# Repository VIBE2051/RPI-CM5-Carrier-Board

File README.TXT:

# CM5 Module PCB with On-Board Cube Module

## Overview
This project involves the design and implementation of a custom PCB featuring the Raspberry Pi Compute Module 5 (CM5) integrated with an on-board Cube module. The PCB is tailored for embedded applications, offering robust connectivity, GPIO access, and flexibility for a wide range of use cases.

## Features
- **Compute Module 5 (CM5) Integration**:
  - Harnesses the power of the Raspberry Pi CM5 for computational tasks.
  - High-density DF40 connectors provide extensive GPIO and peripheral access.

- **On-Board Cube Module**:
  - Supports CubePilot's Cube Module for advanced flight control and navigation.
  - Provides seamless communication between the CM5 and Cube Module.

- **Key Interfaces**:
  - **GPIO Access**: Full access to CM5 GPIOs for customization and flexibility.
  - **Peripheral Support**: Integrated connections for UART, I2C, SPI, CAN, and PWM.
  - **Power Management**: Dedicated power regulation circuits for stable operation.

- **Compact Design**:
  - Optimized for embedded systems with a small form factor.
  - Designed for ease of integration into various enclosures and setups.

## Applications
- **Autonomous Systems**:
  - Ideal for robotics and UAVs requiring compute-intensive processing.
- **IoT Devices**:
  - Suitable for smart devices leveraging Raspberry Pi's ecosystem.
- **Embedded Prototyping**:
  - Flexible platform for developing custom applications.

## Pinout Information
The PCB exposes the GPIOs and other interfaces from the CM5 and Cube Module through accessible connectors. Key pinout details:

- **DF40 Connectors** for CM5:
  - GPIO, UART, I2C, SPI, PWM, and power signals.
  
- **Cube Module DF17 80-Pin Connector**:
  - Interfaces with peripherals such as sensors, GPS, and external modules.

## Design Highlights
- **High-Density Connector Compatibility**:
  - Provides access to all necessary pins while maintaining a clean layout.
- **Grounding and Power Integrity**:
  - Ensures stable operation even in noisy environments.
- **Robust Mounting Points**:
  - Mechanical design supports secure mounting for reliable deployment.

## Getting Started
1. **Assembly**:
   - Populate the PCB with the required components according to the BOM.
   - Insert the CM5 module into its DF40 connector and secure it.
   - Attach the Cube module to the dedicated 80-pin DF17 connector.

2. **Power Up**:
   - Connect a 5V power supply to the designated power input.
   - Verify power integrity using onboard status LEDs.

3. **Development**:
   - Use Raspberry Pi tools to configure and program the CM5.
   - Interface with the Cube module using compatible software (e.g., ArduPilot, PX4).

## Resources
- **Datasheets**:
  - [CM5 Datasheet](https://datasheets.raspberrypi.com/cm5/cm5-datasheet.pdf)
  - [CubePilot Module Pinout](https://docs.cubepilot.org/)
- **KiCad Files**:
  - Schematic and PCB design files are available in the project repository.
- **Software**:
  - Compatible with Raspberry Pi OS and CubePilot firmware.

## Contributing
Contributions to this project are welcome! Please fork the repository and submit a pull request for any improvements or fixes.

## License
This project is licensed under the MIT License. See the LICENSE file for details.

---

**Contact**: For support or inquiries, please contact [your email/organization].

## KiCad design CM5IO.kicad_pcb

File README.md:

# CM5 Module PCB with On-Board Cube Module

## Overview
This project involves the design and implementation of a custom PCB featuring the Raspberry Pi Compute Module 5 (CM5) integrated with an on-board Cube module. The PCB is tailored for embedded applications, offering robust connectivity, GPIO access, and flexibility for a wide range of use cases.

## Features
- **Compute Module 5 (CM5) Integration**:
  - Harnesses the power of the Raspberry Pi CM5 for computational tasks.
  - High-density DF40 connectors provide extensive GPIO and peripheral access.

- **On-Board Cube Module**:
  - Supports CubePilot's Cube Module for advanced flight control and navigation.
  - Provides seamless communication between the CM5 and Cube Module.

- **Key Interfaces**:
  - **GPIO Access**: Full access to CM5 GPIOs for customization and flexibility.
  - **Peripheral Support**: Integrated connections for UART, I2C, SPI, CAN, and PWM.
  - **Power Management**: Dedicated power regulation circuits for stable operation.

- **Compact Design**:
  - Optimized for embedded systems with a small form factor.
  - Designed for ease of integration into various enclosures and setups.

## Applications
- **Autonomous Systems**:
  - Ideal for robotics and UAVs requiring compute-intensive processing.
- **IoT Devices**:
  - Suitable for smart devices leveraging Raspberry Pi's ecosystem.
- **Embedded Prototyping**:
  - Flexible platform for developing custom applications.

## Pinout Information
The PCB exposes the GPIOs and other interfaces from the CM5 and Cube Module through accessible connectors. Key pinout details:

- **DF40 Connectors** for CM5:
  - GPIO, UART, I2C, SPI, PWM, and power signals.
  
- **Cube Module DF17 80-Pin Connector**:
  - Interfaces with peripherals such as sensors, GPS, and external modules.

## Design Highlights
- **High-Density Connector Compatibility**:
  - Provides access to all necessary pins while maintaining a clean layout.
- **Grounding and Power Integrity**:
  - Ensures stable operation even in noisy environments.
- **Robust Mounting Points**:
  - Mechanical design supports secure mounting for reliable deployment.

## Getting Started
1. **Assembly**:
   - Populate the PCB with the required components according to the BOM.
   - Insert the CM5 module into its DF40 connector and secure it.
   - Attach the Cube module to the dedicated 80-pin DF17 connector.

2. **Power Up**:
   - Connect a 5V power supply to the designated power input.
   - Verify power integrity using onboard status LEDs.

3. **Development**:
   - Use Raspberry Pi tools to configure and program the CM5.
   - Interface with the Cube module using compatible software (e.g., ArduPilot, PX4).

## Resources
- **Datasheets**:
  - [CM5 Datasheet](https://datasheets.raspberrypi.com/cm5/cm5-datasheet.pdf)
  - [CubePilot Module Pinout](https://docs.cubepilot.org/)
- **KiCad Files**:
  - Schematic and PCB design files are available in the project repository.
- **Software**:
  - Compatible with Raspberry Pi OS and CubePilot firmware.

## Contributing
Contributions to this project are welcome! Please fork the repository and submit a pull request for any improvements or fixes.

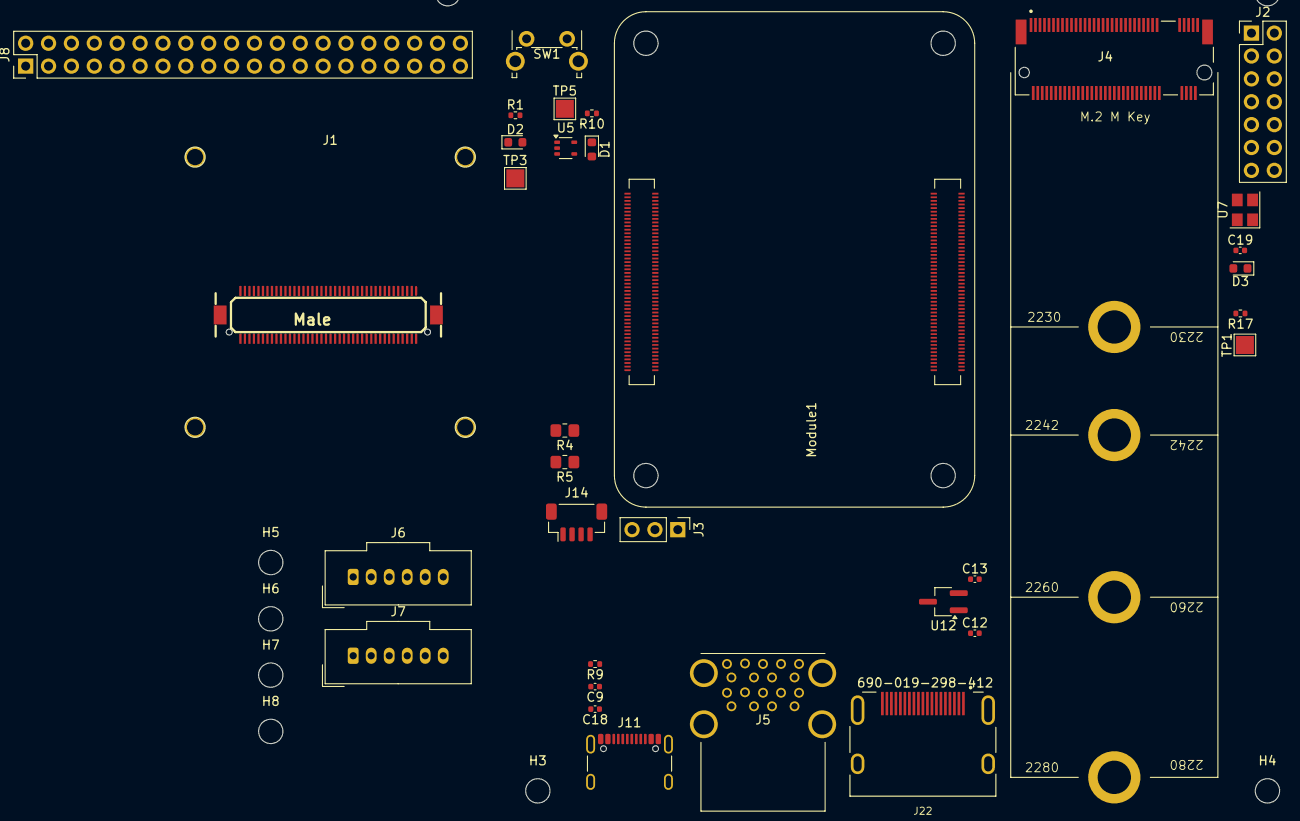
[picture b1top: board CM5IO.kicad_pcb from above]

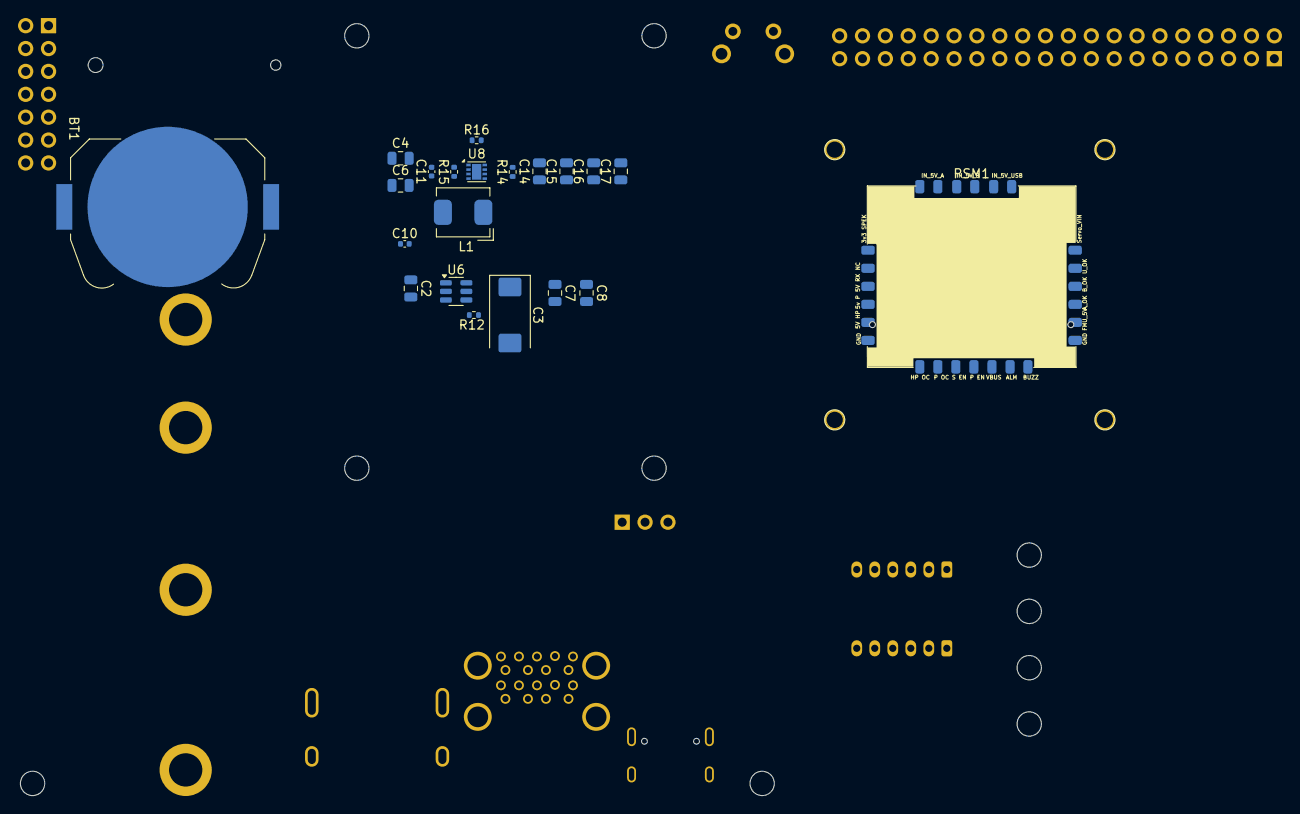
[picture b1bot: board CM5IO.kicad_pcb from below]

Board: 4 copper layers, 62 parts (21 on the bottom side), 105 nets, no tracks yet.

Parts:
BT1: Battery_Cell; BatteryHolder_Keystone_3034_1x20mm
C2, C4, C6, C7, C8, C14, C15, C16, C17: 10u; C_0805_2012Metric
C3: 100uF; CP_EIA-7343-31_Kemet-D
C9, C10, C12, C13, C18, C19: 100n; C_0402_1005Metric
C11: 4.7nF; C_0402_1005Metric
D1: LED Red; LED_0603_1608Metric
D2, D3: LED Green; LED_0603_1608Metric
H1, H2, H3, H4, H5, H6, H7, H8: MountingHole; MountingHole_2.7mm_M2.5_DIN965
J1: DF17_1.0H_-80DP-0.5V_57_; CON-DF17-80M
J2: Conn_02x07_Odd_Even; PinHeader_2x07_P2.54mm_Vertical
J3: Conn_01x03; PinHeader_1x03_P2.54mm_Vertical
J4: Bus_M.2_Socket_M; M.2 M Key socket
J5: USB3_A; MTCONN_UBAF30-D2011
J6, J7: Conn_01x06_Socket; Molex_MicroClasp_55932-0630_1x06_P2.00mm_Vertical
J8: THD-20-R; PinHeader_2x20_P2.54mm_Vertical
J11: USB_C_Receptacle_USB2.0; USB_C_Receptacle_GCT_USB4105-xx-A_16P_TopMnt_Horizontal
J14: JST_SHBM04B-SRSS-TB; JST_SH_BM04B-SRSS-TB_1x04-1MP_P1.00mm_Vertical
J22: 690-019-298-412; EDAC 690-019-298-412
L1: 2.2uH; L_Bourns_SRP5030CC
Module1: ComputeModule5-CM5; Raspberry-Pi-5-Compute-Module
PSM1: Power Selection module; PSM
R1, R10, R17: 1k; R_0402_1005Metric
R4: nf; R_0805_2012Metric_Pad1.20x1.40mm_HandSolder
R5: 0R; R_0805_2012Metric_Pad1.20x1.40mm_HandSolder
R9, R16: 2.2K 1%; R_0402_1005Metric
R12: 15K 1%; R_0402_1005Metric
R14: 100K 1%; R_0402_1005Metric
R15: 10K 1%; R_0402_1005Metric
SW1: Right angle Tact button; SW_Tactile_SPST_Angled_PTS645Vx58-2LFS
TP1, TP3, TP5: TestPoint; TestPoint_Pad_2.0x2.0mm
U5: 74LVC1G07SE-7; SOT-353_SC-70-5
U6: AP22653W6; SOT-23-6
U7: ASEK-32.768KHZ-L-R-T; Crystal_SMD_3225-4Pin_3.2x2.5mm
U8: AP3441SHE-7B; DFN-8-1EP_2x2mm_P0.5mm_EP1.05x1.75mm
U12: RT9742SNGV; TSOT-23_HandSoldering

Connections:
/+3.3v: D1.2 (A), D2.2 (A), J8.1, J8.17, Module1.84 (+3.3v_(Output)), Module1.86 (+3.3v_(Output)), R5.1, U5.5 (VCC)
/+5v: C2.1, C4.1, C6.1, C9.1, C10.1, C12.1, C18.1, J8.2, J8.4, J11.A4 (VBUS), J11.A9 (VBUS), J11.B4 (VBUS), J11.B9 (VBUS), J14.1, Module1.77 (+5v_(Input)), Module1.79 (+5v_(Input)), Module1.81 (+5v_(Input)), Module1.83 (+5v_(Input)), Module1.85 (+5v_(Input)), Module1.87 (+5v_(Input)), R9.1, U6.1 (IN), U8.3 (VIN), U12.1 (IN)
/CC1: J11.A5 (CC1), Module1.94 (CC1)
/CC2: J11.B5 (CC2), Module1.96 (CC2)
/CM5_GPIO ( Ethernet, GPIO, SDCARD)/+1.8v: Module1.88 (+1.8v_(Output)), Module1.90 (+1.8v_(Output)), R4.1
/CM5_GPIO ( Ethernet, GPIO, SDCARD)/BT_nDis: J3.3, Module1.91 (BT_nDisable)
/CM5_GPIO ( Ethernet, GPIO, SDCARD)/Cube_PSM_GPIO/BUZZER_OUT: J7.5, PSM1.BUZZER_OUT (BUZZ_OUT)
/CM5_GPIO ( Ethernet, GPIO, SDCARD)/Cube_PSM_GPIO/VDD_5V_BRICK: J6.1, J6.2, PSM1.VDD_BRICK_IN
/CM5_GPIO ( Ethernet, GPIO, SDCARD)/EEPROM_nWP: J2.4, Module1.20 (EEPROM_nWP)
/CM5_GPIO ( Ethernet, GPIO, SDCARD)/GPIO2: J8.3, Module1.58 (GPIO2)
/CM5_GPIO ( Ethernet, GPIO, SDCARD)/GPIO3: J8.5, Module1.56 (GPIO3)
/CM5_GPIO ( Ethernet, GPIO, SDCARD)/GPIO4: J8.7, Module1.54 (GPIO4)
/CM5_GPIO ( Ethernet, GPIO, SDCARD)/GPIO5: J8.29, Module1.34 (GPIO5)
/CM5_GPIO ( Ethernet, GPIO, SDCARD)/GPIO6: J8.31, Module1.30 (GPIO6)
/CM5_GPIO ( Ethernet, GPIO, SDCARD)/GPIO7: J8.26, Module1.37 (GPIO7)
/CM5_GPIO ( Ethernet, GPIO, SDCARD)/GPIO8: J8.24, Module1.39 (GPIO8)
/CM5_GPIO ( Ethernet, GPIO, SDCARD)/GPIO9: J8.21, Module1.40 (GPIO9)
/CM5_GPIO ( Ethernet, GPIO, SDCARD)/GPIO10: J8.19, Module1.44 (GPIO10)
/CM5_GPIO ( Ethernet, GPIO, SDCARD)/GPIO11: J8.23, Module1.38 (GPIO11)
/CM5_GPIO ( Ethernet, GPIO, SDCARD)/GPIO12: J8.32, Module1.31 (GPIO12)
/CM5_GPIO ( Ethernet, GPIO, SDCARD)/GPIO13: J8.33, Module1.28 (GPIO13)
/CM5_GPIO ( Ethernet, GPIO, SDCARD)/GPIO14: J8.8, Module1.55 (GPIO14)
/CM5_GPIO ( Ethernet, GPIO, SDCARD)/GPIO15: J8.10, Module1.51 (GPIO15)
/CM5_GPIO ( Ethernet, GPIO, SDCARD)/GPIO16: J8.36, Module1.29 (GPIO16)
/CM5_GPIO ( Ethernet, GPIO, SDCARD)/GPIO17: J8.11, Module1.50 (GPIO17)
/CM5_GPIO ( Ethernet, GPIO, SDCARD)/GPIO18: J8.12, Module1.49 (GPIO18)
/CM5_GPIO ( Ethernet, GPIO, SDCARD)/GPIO19: J8.35, Module1.26 (GPIO19)
/CM5_GPIO ( Ethernet, GPIO, SDCARD)/GPIO20: J8.38, Module1.27 (GPIO20)
/CM5_GPIO ( Ethernet, GPIO, SDCARD)/GPIO21: J8.40, Module1.25 (GPIO21)
/CM5_GPIO ( Ethernet, GPIO, SDCARD)/GPIO22: J8.15, Module1.46 (GPIO22)
/CM5_GPIO ( Ethernet, GPIO, SDCARD)/GPIO23: J8.16, Module1.47 (GPIO23)
/CM5_GPIO ( Ethernet, GPIO, SDCARD)/GPIO24: J8.18, Module1.45 (GPIO24)
/CM5_GPIO ( Ethernet, GPIO, SDCARD)/GPIO25: J8.22, Module1.41 (GPIO25)
/CM5_GPIO ( Ethernet, GPIO, SDCARD)/GPIO26: J8.37, Module1.24 (GPIO26)
/CM5_GPIO ( Ethernet, GPIO, SDCARD)/GPIO27: J8.13, Module1.48 (GPIO27)
/CM5_GPIO ( Ethernet, GPIO, SDCARD)/GPIO_VREF: Module1.78 (GPIO_VREF(1.8v/3.3v_Input)), R4.2, R5.2
/CM5_GPIO ( Ethernet, GPIO, SDCARD)/ID_SC: J8.28, Module1.35 (ID_SC)
/CM5_GPIO ( Ethernet, GPIO, SDCARD)/ID_SD: J8.27, Module1.36 (ID_SD)
/CM5_GPIO ( Ethernet, GPIO, SDCARD)/PMIC_ENABLE: J2.12, Module1.99 (PMIC_ENABLE)
/CM5_GPIO ( Ethernet, GPIO, SDCARD)/PWM: J14.2, Module1.19 (FAN_PWM)
/CM5_GPIO ( Ethernet, GPIO, SDCARD)/PWR_BUT: J2.14, Module1.92 (PWR_BUT), SW1.1
/CM5_GPIO ( Ethernet, GPIO, SDCARD)/SYNC_OUT: J2.6, Module1.18 (Ethernet_SYNC_OUT(3.3v))
/CM5_GPIO ( Ethernet, GPIO, SDCARD)/TACHO: J14.4, Module1.16 (FAN_TACHO)
/CM5_GPIO ( Ethernet, GPIO, SDCARD)/USBOTG: J2.10, Module1.101 (USB_OTG_ID)
/CM5_GPIO ( Ethernet, GPIO, SDCARD)/VBAT: BT1.1 (+), Module1.76 (VBAT)
/CM5_GPIO ( Ethernet, GPIO, SDCARD)/WL_nDis: J3.1, Module1.89 (WiFi_nDisable)
/CM5_GPIO ( Ethernet, GPIO, SDCARD)/nPWR_LED: Module1.95 (LED_nPWR), U5.2
/CM5_GPIO ( Ethernet, GPIO, SDCARD)/nRPIBOOT: J2.2, Module1.93 (nRPIBOOT)
/CM5_HighSpeed/HDMI0_CEC: J22.13 (CEC), Module1.151 (HDMI0_CEC)
/CM5_HighSpeed/HDMI0_CK_N: J22.12 (CK-), Module1.190 (HDMI0_CLK_N)
/CM5_HighSpeed/HDMI0_CK_P: J22.10 (CK+), Module1.188 (HDMI0_CLK_P)
/CM5_HighSpeed/HDMI0_D0_N: J22.9 (D0-), Module1.184 (HDMI0_TX0_N)
/CM5_HighSpeed/HDMI0_D0_P: J22.7 (D0+), Module1.182 (HDMI0_TX0_P)
/CM5_HighSpeed/HDMI0_D1_N: J22.6 (D1-), Module1.178 (HDMI0_TX1_N)
/CM5_HighSpeed/HDMI0_D1_P: J22.4 (D1+), Module1.176 (HDMI0_TX1_P)
/CM5_HighSpeed/HDMI0_D2_N: J22.3 (D2-), Module1.172 (HDMI0_TX2_N)
/CM5_HighSpeed/HDMI0_D2_P: J22.1 (D2+), Module1.170 (HDMI0_TX2_P)
/CM5_HighSpeed/HDMI0_HOTPLUG: J22.19 (HPD/HEAC-), Module1.153 (HDMI0_HOTPLUG)
/CM5_HighSpeed/HDMI0_SCL: J22.15 (SCL), Module1.200 (HDMI0_SCL)
/CM5_HighSpeed/HDMI0_SDA: J22.16 (SDA), Module1.199 (HDMI0_SDA)
/CM5_HighSpeed/HDMI_5v: C13.1, J22.18 (+5V), U12.2 (OUT)
/CM5_HighSpeed/PCIE_CLK_N: J4.53 (REFCLKn), Module1.112 (PCIe_CLK_N)
/CM5_HighSpeed/PCIE_CLK_P: J4.55 (REFCLKp), Module1.110 (PCIe_CLK_P)
/CM5_HighSpeed/PCIE_PWR_EN: Module1.106 (PCIE_PWR_EN), R14.1, U8.7 (EN)
/CM5_HighSpeed/PCIE_RX_N: J4.43 (PETp0), Module1.118 (PCIe_RX_N)
/CM5_HighSpeed/PCIE_RX_P: J4.41 (PETn0), Module1.116 (PCIe_RX_P)
/CM5_HighSpeed/PCIE_TX_N: J4.49 (PERp0), Module1.124 (PCIe_TX_N)
/CM5_HighSpeed/PCIE_TX_P: J4.47 (PERn0), Module1.122 (PCIe_TX_P)
/CM5_HighSpeed/PCIE_nCLKREQ: J4.52 (~CLKREQ), Module1.102 (PCIe_nCLKREQ)
/CM5_HighSpeed/PCIE_nRST: J4.50 (~PERST), Module1.109 (PCIe_nRST)
/CM5_HighSpeed/PCIE_nWAKE: J4.54 (~PEWAKE), Module1.104 (PCIE_nWAKE)
/CM5_HighSpeed/USB3-0-D_N: J5.A2 (D-), Module1.136 (USB3-0-D_N)
/CM5_HighSpeed/USB3-0-D_P: J5.A3 (D+), Module1.134 (USB3-0-D_P)
/CM5_HighSpeed/USB3-0-RX_N: J5.A6 (SSRX+), Module1.128 (USB3-0-RX_N)
/CM5_HighSpeed/USB3-0-RX_P: J5.A5 (SSRX-), Module1.130 (USB3-0-RX_P)
/CM5_HighSpeed/USB3-0-TX_N: J5.A9 (SSTX+), Module1.140 (USB3-0-TX_N)
/CM5_HighSpeed/USB3-0-TX_P: J5.A8 (SSTX-), Module1.142 (USB3-0-TX_P)
/CM5_HighSpeed/USB3-1-D_N: J5.B2 (D-), Module1.165 (USB3-1-D_N)
/CM5_HighSpeed/USB3-1-D_P: J5.B3 (D+), Module1.163 (USB3-1-D_P)
/CM5_HighSpeed/USB3-1-RX_N: J5.B6 (SSRX+), Module1.157 (USB3-1-RX_N)
/CM5_HighSpeed/USB3-1-RX_P: J5.B5 (SSRX-), Module1.159 (USB3-1-RX_P)
/CM5_HighSpeed/USB3-1-TX_N: J5.B9 (SSTX+), Module1.169 (USB3-1-TX_N)
/CM5_HighSpeed/USB3-1-TX_P: J5.B8 (SSTX-), Module1.171 (USB3-1-TX_P)
/CM5_HighSpeed/VBUS: C3.1, C7.1, C8.1, J5.A1 (VBUS), J5.B1 (VBUS), U6.6 (OUT)
/CM5_HighSpeed/VBUS_EN: Module1.111 (VBUS_EN), U6.3 (EN)
/PCIe-M2/FB: C11.2, R15.2, R16.1, U8.1 (FB)
/PCIe-M2/M2_3v3: C11.1, C14.1, C15.1, C16.1, C17.1, C19.1, D3.2 (A), J4.2 (3.3V), J4.4 (3.3V), J4.12 (3.3V), J4.14 (3.3V), J4.16 (3.3V), J4.18 (3.3V), J4.70 (3.3V), J4.72 (3.3V), J4.74 (3.3V), L1.2, R15.1, U7.1 (EN), U7.4 (VDD)
/USB2_N: J11.A7 (D-), J11.B7 (D-), Module1.103 (USB2_N)
/USB2_P: J11.A6 (D+), J11.B6 (D+), Module1.105 (USB2_P)
ALARM: J1.24, PSM1.ALARM
GND: BT1.2 (-), C2.2, C3.2, C4.2, C6.2, C7.2, C8.2, C9.2, C10.2, C12.2, C13.2, C14.2, C15.2, C16.2, C17.2, C18.2, C19.2, J1.13, J1.15, J2.1, J2.3, J2.5, J2.7, J2.9, J2.11, J2.13, J3.2, J4.1 (GND), J4.3 (GND), J4.9 (GND), J4.15 (GND), J4.21 (GND), J4.27 (GND), J4.33 (GND), J4.39 (GND), J4.45 (GND), J4.51 (GND), J4.57 (GND), J4.71 (GND), J4.73 (GND), J4.75 (GND), J4.M1 (GND2230), J4.M2 (GND2242), J4.M3 (GND2260), J4.M4 (GND2280), J4.S1, J4.S2, J5.A4 (GND), J5.A7 (DRAIN), J5.B4 (GND), J5.B7 (DRAIN), J6.5, J6.6, J7.4, J8.6, J8.9, J8.14, J8.20, J8.25, J8.30, J8.34, J8.39, J11.A1 (GND), J11.A12 (GND), J11.B1 (GND), J11.B12 (GND), J11.S1 (SHIELD), J14.3, J22.2 (D2S), J22.5 (D1S), J22.8 (D0S), J22.11 (CKS), J22.17 (GND), J22.SH1 (SH), J22.SH2 (SH), J22.SH3 (SH), J22.SH4 (SH), Module1.1 (GND), Module1.2 (GND), Module1.7 (GND), Module1.8 (GND), Module1.13 (GND), Module1.14 (GND), Module1.22 (GND), Module1.23 (GND), Module1.32 (GND), Module1.33 (GND), Module1.42 (GND), Module1.43 (GND), Module1.52 (GND), Module1.53 (GND), Module1.59 (GND), Module1.60 (GND), Module1.65 (GND), Module1.66 (GND), Module1.71 (GND), Module1.74 (GND), Module1.98 (GND), Module1.107 (GND), Module1.108 (GND), Module1.113 (GND), Module1.114 (GND), Module1.119 (GND), Module1.120 (GND), Module1.125 (GND), Module1.126 (GND), Module1.131 (GND), Module1.132 (GND), Module1.137 (GND), Module1.138 (GND), Module1.144 (GND), Module1.150 (GND), Module1.155 (GND), Module1.156 (GND), Module1.161 (GND), Module1.162 (GND), Module1.167 (GND), Module1.168 (GND), Module1.173 (GND), Module1.174 (GND), Module1.179 (GND), Module1.180 (GND), Module1.185 (GND), Module1.186 (GND), Module1.191 (GND), Module1.192 (GND), Module1.197 (GND), Module1.198 (GND), PSM1.GND, R9.2, R12.2, R14.2, R16.2, SW1.2, U5.3 (GND), U6.2 (GND), U7.2 (GND), U8.4 (PGND), U8.8 (SGND), U8.9 (PAD), U12.3 (GND)
I2C_2_SDA: J1.4, J1.6
unnamed: D1.1 (K), R10.1, TP5.1
unnamed: D2.1 (K), R1.1, TP3.1
unnamed: D3.1 (K), R17.1, TP1.1
unnamed: J4.10 (DAS/~DSS/~LED1), R17.2
unnamed: J4.68 (SUSCLK), U7.3 (Out)
unnamed: Module1.21 (LED_nACT), R1.2
unnamed: R10.2, U5.4
unnamed: R12.1, U6.5 (ILIM)
unnamed: L1.1, U8.6 (LX)
OTG_DM1: J1.33, J7.3
OTG_DP1: J1.31, J7.2
VBUS: J1.29, J7.1, PSM1.VDD_VBUS
VDD 5V IN PROT: J1.61, J1.63

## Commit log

2024-12-11 Removing unwanted sections, such that the carrier board is a blank canvas
2024-12-13 Added USB SS type A, thinking of replacing it in the future with USB type-c
2024-12-13 Board development
2024-12-15 Intitial commit for CM5xCube PCB
2024-12-16 Included Cube pilot schematic symbol, pcb footprint and created another sheet.
2024-12-16 readme updated
2024-12-16 read me updated
2024-12-23 Connection for FC labelled
2024-12-23 Added power plugs, still need decide whether power with come from the PI or separate source
2024-12-23 Included a git ignore file
2024-12-23 PCB Layout edited
